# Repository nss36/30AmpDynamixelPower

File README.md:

# 30AmpDynamixelPower
Nicholas Szczecinski 2018
Case Western Reserve University
Cleveland, Ohio, USA

EAGLE files for a power distributor to source 12V, 30A for multiple Dynamixel AX/MX Series smart servos.

Here are the components you need, with Digikey part numbers:
1 Terminal block - 277-5840-ND
1 Fuse block - 36-3557-2-ND
1 30A fuse - F5046-ND
1 Pushbutton switch - CW181-ND
1 30A relay - 255-1719-ND
8 MOLEX 22-03-5035 sockets - WM18887-ND

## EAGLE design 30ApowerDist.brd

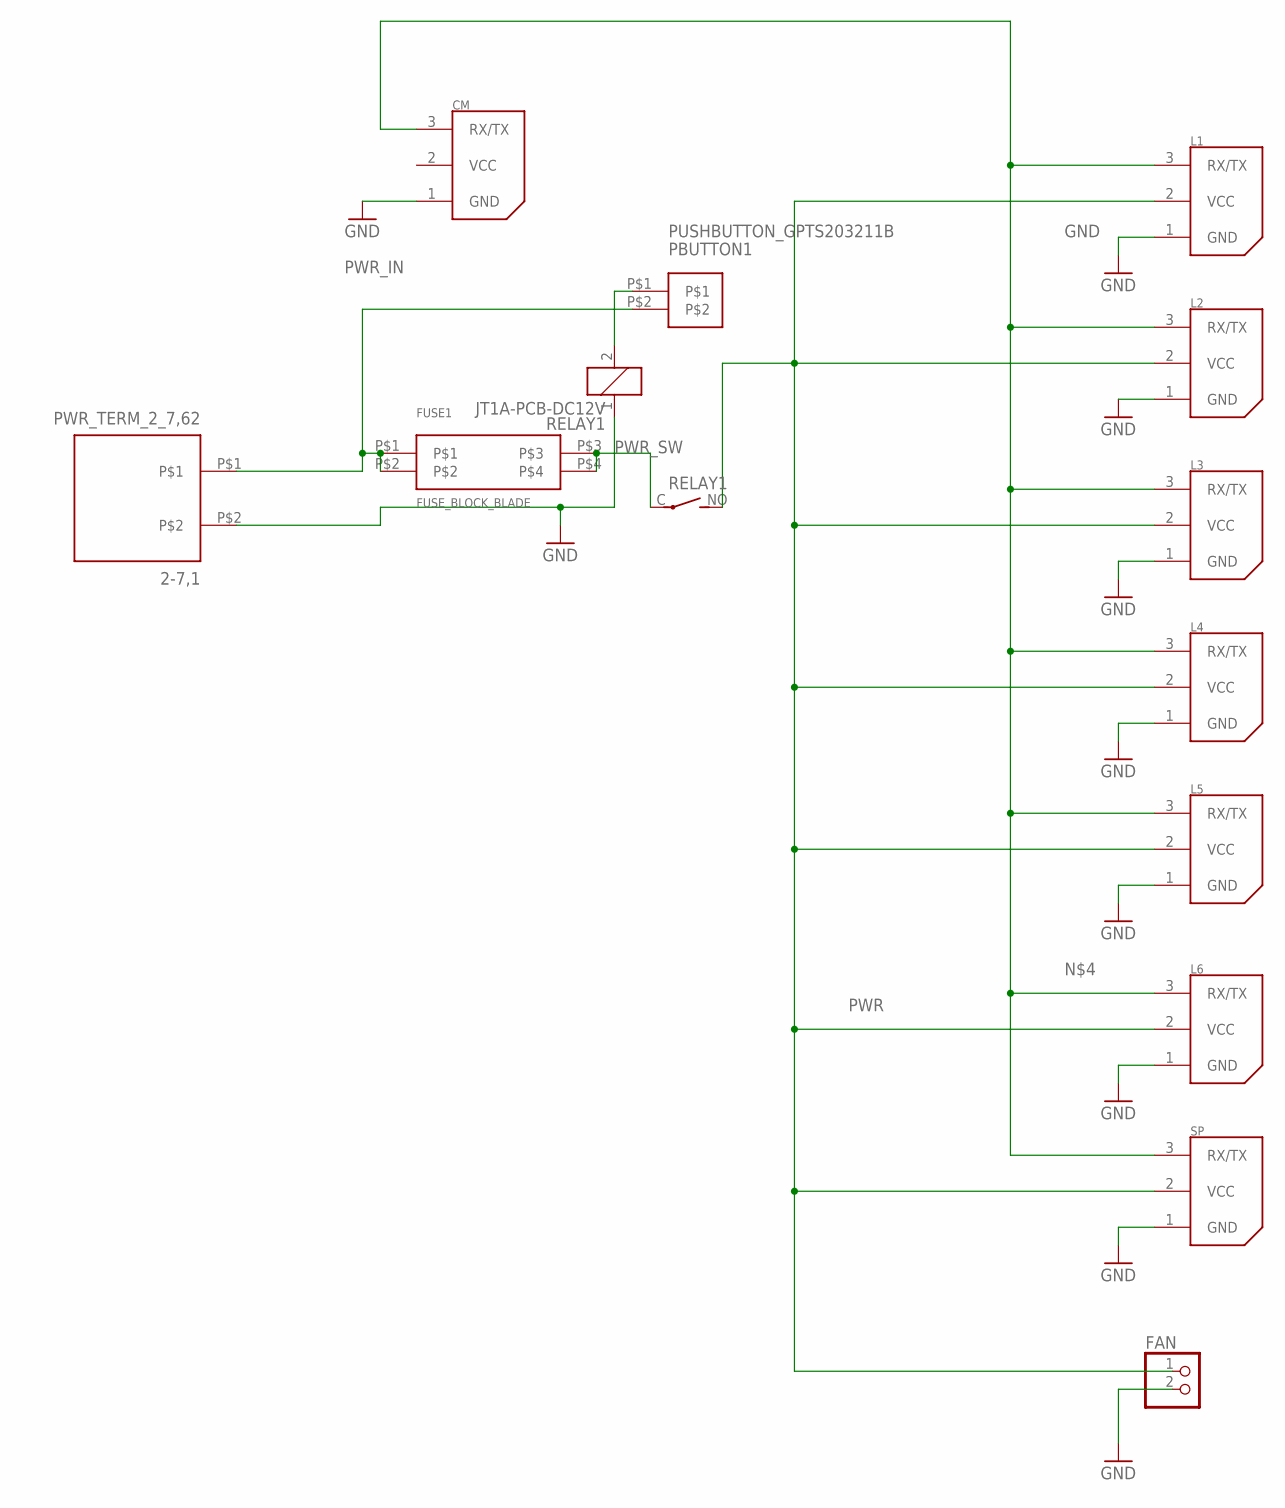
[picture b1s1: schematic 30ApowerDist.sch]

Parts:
2-7,1: PWR_TERM_2_7,62
CM: 22-03-5035; 5267-3
FAN: PINHD-1X2; 1X02
FUSE1: FUSE_BLOCK_BLADE
L1, L2, L3, L4, L5, L6: 22-03-5035; 5267-3
PBUTTON1: PUSHBUTTON_GPTS203211B
RELAY1: JT1A-PCB-DC12V; JT1A-PCB
SP: 22-03-5035; 5267-3

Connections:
GND: 2-7,1.P$2, CM.1 (GND), FAN.2, L1.1 (GND), L2.1 (GND), L3.1 (GND), L4.1 (GND), L5.1 (GND), L6.1 (GND), RELAY1.1, SP.1 (GND)
unnamed: PBUTTON1.P$1, RELAY1.2
unnamed: CM.3 (RX/TX), L1.3 (RX/TX), L2.3 (RX/TX), L3.3 (RX/TX), L4.3 (RX/TX), L5.3 (RX/TX), L6.3 (RX/TX), SP.3 (RX/TX)
PWR: FAN.1, L1.2 (VCC), L2.2 (VCC), L3.2 (VCC), L4.2 (VCC), L5.2 (VCC), L6.2 (VCC), RELAY1.NO (S), SP.2 (VCC)
PWR_IN: 2-7,1.P$1, FUSE1.P$1, FUSE1.P$2, PBUTTON1.P$2
PWR_SW: FUSE1.P$3, FUSE1.P$4, RELAY1.C

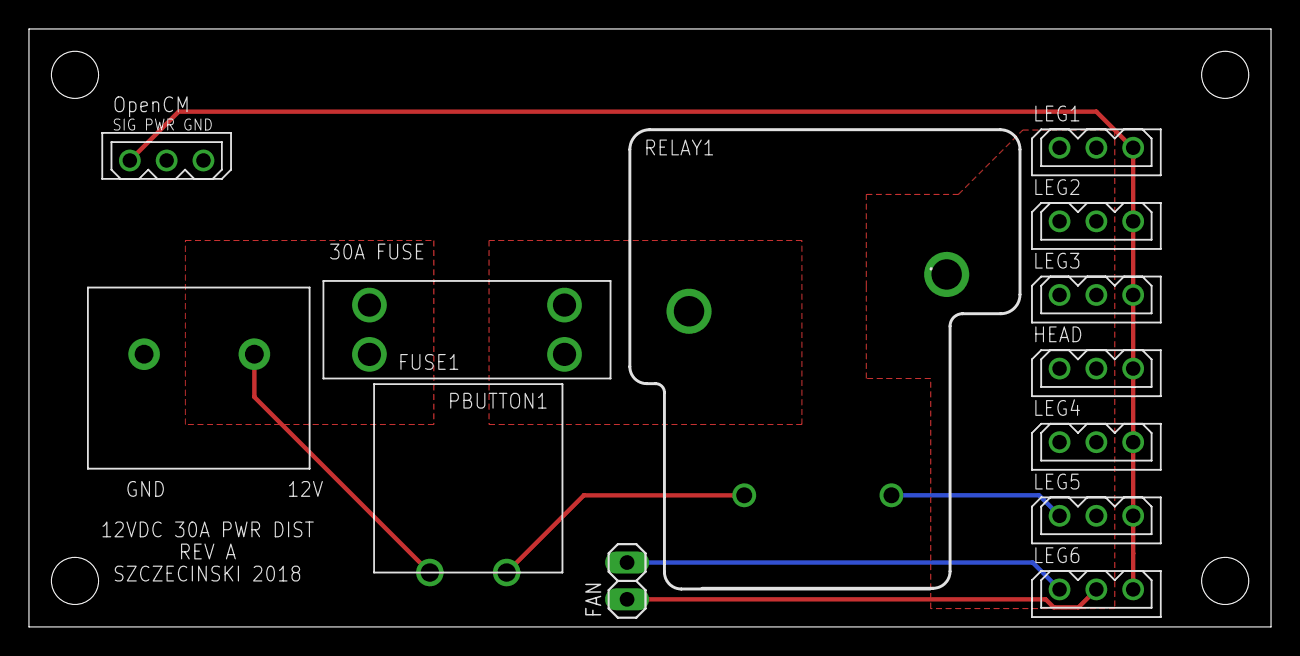
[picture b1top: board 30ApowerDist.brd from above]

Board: 2 copper layers, 85.7 x 41.3 mm, 13 parts (0 on the bottom side), 6 nets.

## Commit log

2018-12-10 Added EAGLE design files and CAM files
